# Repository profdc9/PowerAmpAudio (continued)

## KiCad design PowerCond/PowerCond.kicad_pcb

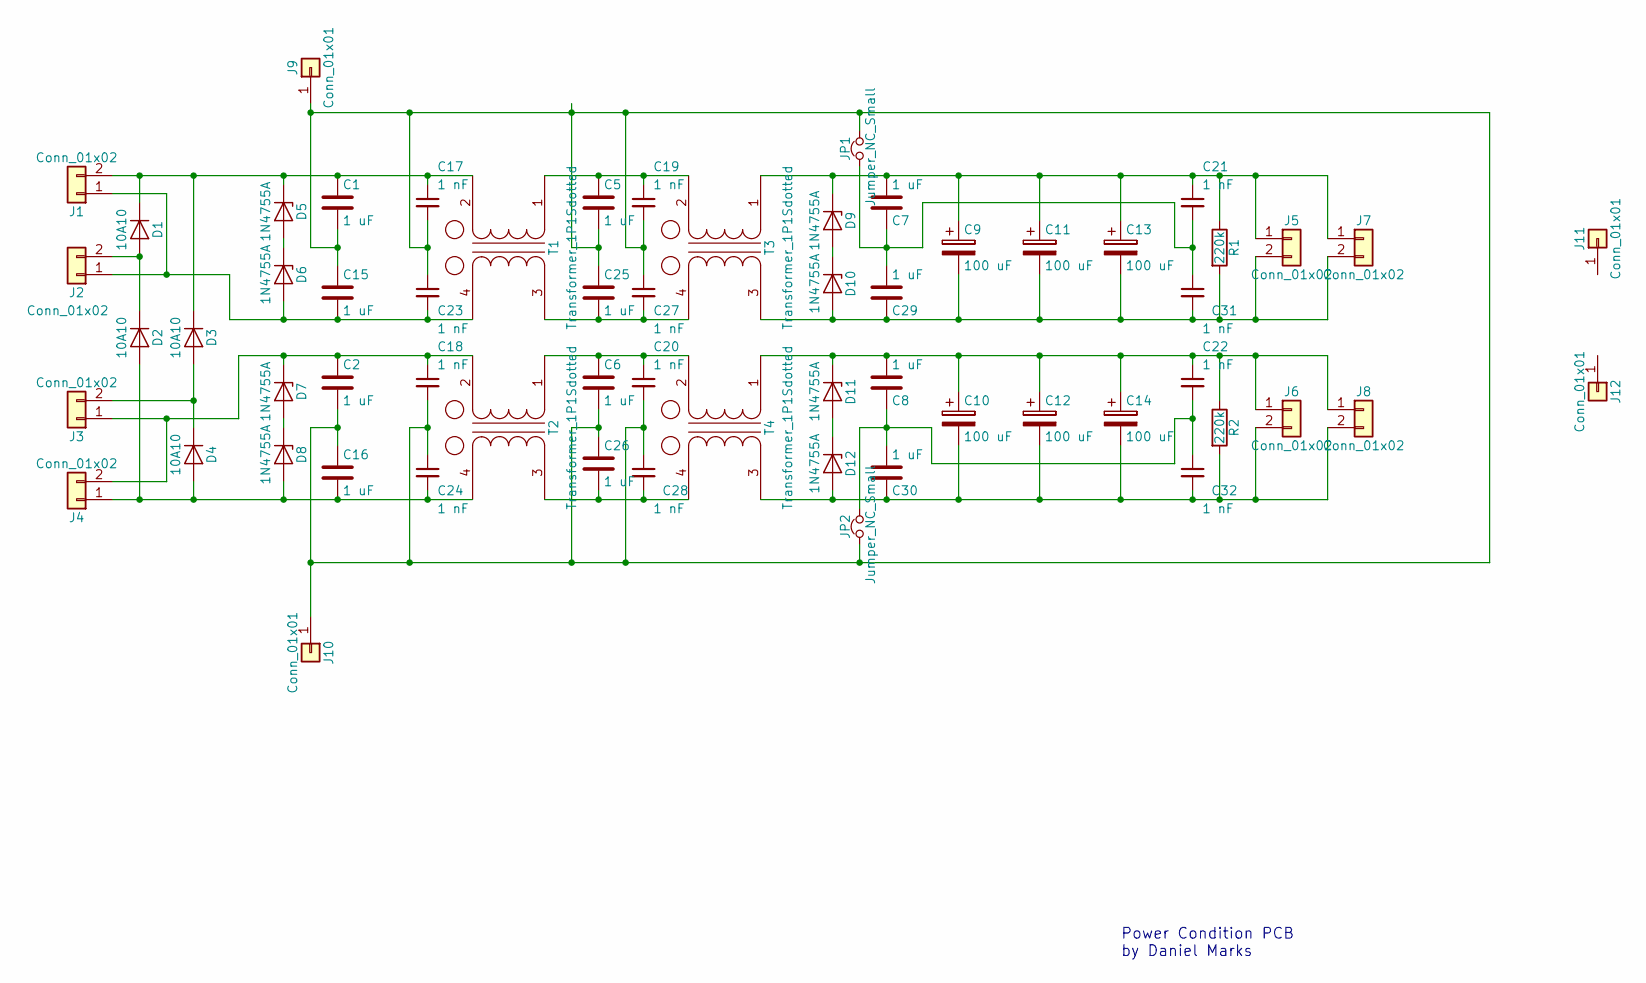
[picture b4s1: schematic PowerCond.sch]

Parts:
C1, C2, C5, C6, C7, C8, C15, C16, C25, C26, C29, C30: 1 uF; C_Axial_L5.1mm_D3.1mm_P12.50mm_Horizontal; LCSC C178471
C9, C10, C11, C12, C13, C14: 100 uF; CP_Radial_D14.0mm_P7.50mm; LCSC C330940
C17, C18, C20, C21, C22, C23, C24, C27, C28, C31, C32: 1 nF; C_Disc_D5.0mm_W2.5mm_P5.00mm; LCSC C249151
C19: 1 nF; C_Disc_D5.0mm_W2.5mm_P5.00mm
D1, D2, D3, D4: 10A10; D_P600_R-6_P12.70mm_Horizontal; LCSC C106904
D5, D6, D7, D8, D9, D10, D11, D12: 1N4755A; D_DO-41_SOD81_P7.62mm_Horizontal; LCSC C8043
J1, J2, J3, J4, J5, J6, J7, J8: Conn_01x02; TerminalBlock_bornier-2_P5.08mm_with_spade; LCSC C395849
J9, J10, J11, J12: Conn_01x01; 1pin
JP1, JP2: Jumper_NC_Small; Pin_Header_Straight_1x02_Pitch2.54mm
R1, R2: 220k; R_Axial_DIN0309_L9.0mm_D3.2mm_P12.70mm_Horizontal
T1, T2, T4: Transformer_1P1Sdotted; GenericCMCL3
T3: Transformer_1P1Sdotted; GenericCMCL3; LCSC C249151

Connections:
unnamed: C1.1, C17.1, D1.1 (K), D3.1 (K), D5.1 (K), J1.2, T1.2 (AB)
unnamed: C1.2, C2.2, C5.2, C6.2, C15.1, C16.1, C17.2, C18.2, C19.2, C20.2, C23.1, C24.1, C25.1, C26.1, C27.1, C28.1, J9.1, J10.1, JP1.2, JP2.1
unnamed: C8.2, C10.1, C12.1, C14.1, C22.1, D11.1 (K), J6.1, J8.1, R2.1, T4.1 (AA)
unnamed: C10.2, C12.2, C14.2, C30.1, C32.2, D12.2 (A), J6.2, J8.2, R2.2, T4.3 (SA)
unnamed: C7.2, C9.1, C11.1, C13.1, C21.1, D9.1 (K), J5.1, J7.1, R1.1, T3.1 (AA)
unnamed: C9.2, C11.2, C13.2, C29.1, C31.2, D10.2 (A), J5.2, J7.2, R1.2, T3.3 (SA)
unnamed: C15.2, C23.2, D6.2 (A), J1.1, J2.1, T1.4 (SB)
unnamed: C16.2, C24.2, D2.2 (A), D4.2 (A), D8.2 (A), J4.1, T2.4 (SB)
unnamed: C2.1, C18.1, D7.1 (K), J3.1, J4.2, T2.2 (AB)
unnamed: C5.1, C19.1, T1.1 (AA), T3.2 (AB)
unnamed: C6.1, C20.1, T2.1 (AA), T4.2 (AB)
unnamed: C7.1, C21.2, C29.2, C31.1, JP1.1
unnamed: C8.1, C22.2, C30.2, C32.1, JP2.2
unnamed: C25.2, C27.2, T1.3 (SA), T3.4 (SB)
unnamed: C26.2, C28.2, T2.3 (SA), T4.4 (SB)
unnamed: D1.2 (A), D2.1 (K), J2.2
unnamed: D3.2 (A), D4.1 (K), J3.2
unnamed: D5.2 (A), D6.1 (K)
unnamed: D7.2 (A), D8.1 (K)
unnamed: D9.2 (A), D10.1 (K)
unnamed: D11.2 (A), D12.1 (K)

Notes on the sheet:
Power Condition PCB by Daniel Marks

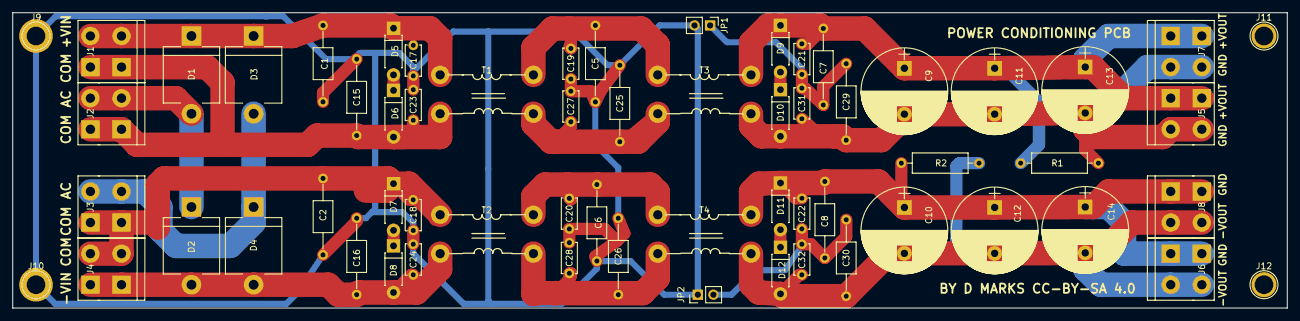
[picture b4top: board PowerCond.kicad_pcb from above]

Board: 2 copper layers, 208.3 x 48.3 mm, 62 parts (0 on the bottom side), 21 nets.

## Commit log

2020-08-18 Added power condition board
2020-08-19 Added XLRtoBal
2020-08-20 Fixed XLR footprint
2020-08-20 Changed bootstrap capacitor
2020-08-21 Added credit where credit is due
2020-08-22 Added soft start circuit
2020-08-25 Submitted to JLCPCB 2020-08-24
2020-08-25 Added BOM
2020-08-26 Fixed nasty bug in soft start
2020-09-07 Changed softstart and Poweramp to TO-220 transistors
2020-09-16 Changed to 2N5551/2N5401 from BC546C/BC556C transistors
2020-09-18 Some more layout changed and XlrtoBal fix
2020-09-21 JLCPCB order 2020-09-21
2020-10-12 Working design 2020-10-12
2020-10-13 Changed grounding and star layout
2020-10-14 Sample feedback from output directly
2020-10-14 Moved Q1 and Q2 together
2020-10-14 Redid gerbers and files
2020-10-17 Added instructions
2020-10-17 More README.md
2020-10-18 Added option for spade terminal power connections
2020-10-18 Added Simulations
2020-10-20 Added OITPC compensation
2020-10-20 Added drill pattern template
2020-10-22 Redid star scheme again, added grounding diagram, modified drill template
2020-11-01 Changed components for lower quiescent power
2020-11-19 Added base stopper resistors
2021-01-03 Modified soft start to have wire jumper over resistors
2021-05-05 Additions of optional zener diodes to limit current surges
2021-05-11 Changed to use optotriac shutoff of bias
2021-06-06 Added back Q9 transistor for Q8 protection
2021-06-25 Added the PowerampSimpleParts version with TIP41/42
2021-06-28 Minor tweaks to PowerampSimpleParts
2021-08-11 A few minor tweaks to PowerampSimpleParts layout
2022-02-24 Fixed some silkscreening
2022-02-24 Fixed images
2022-05-03 Updated gerbers
2022-05-05 Thickened traces on XLRtoBal board
